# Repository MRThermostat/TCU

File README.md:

# TCU
hardware/software for thermostat control unit

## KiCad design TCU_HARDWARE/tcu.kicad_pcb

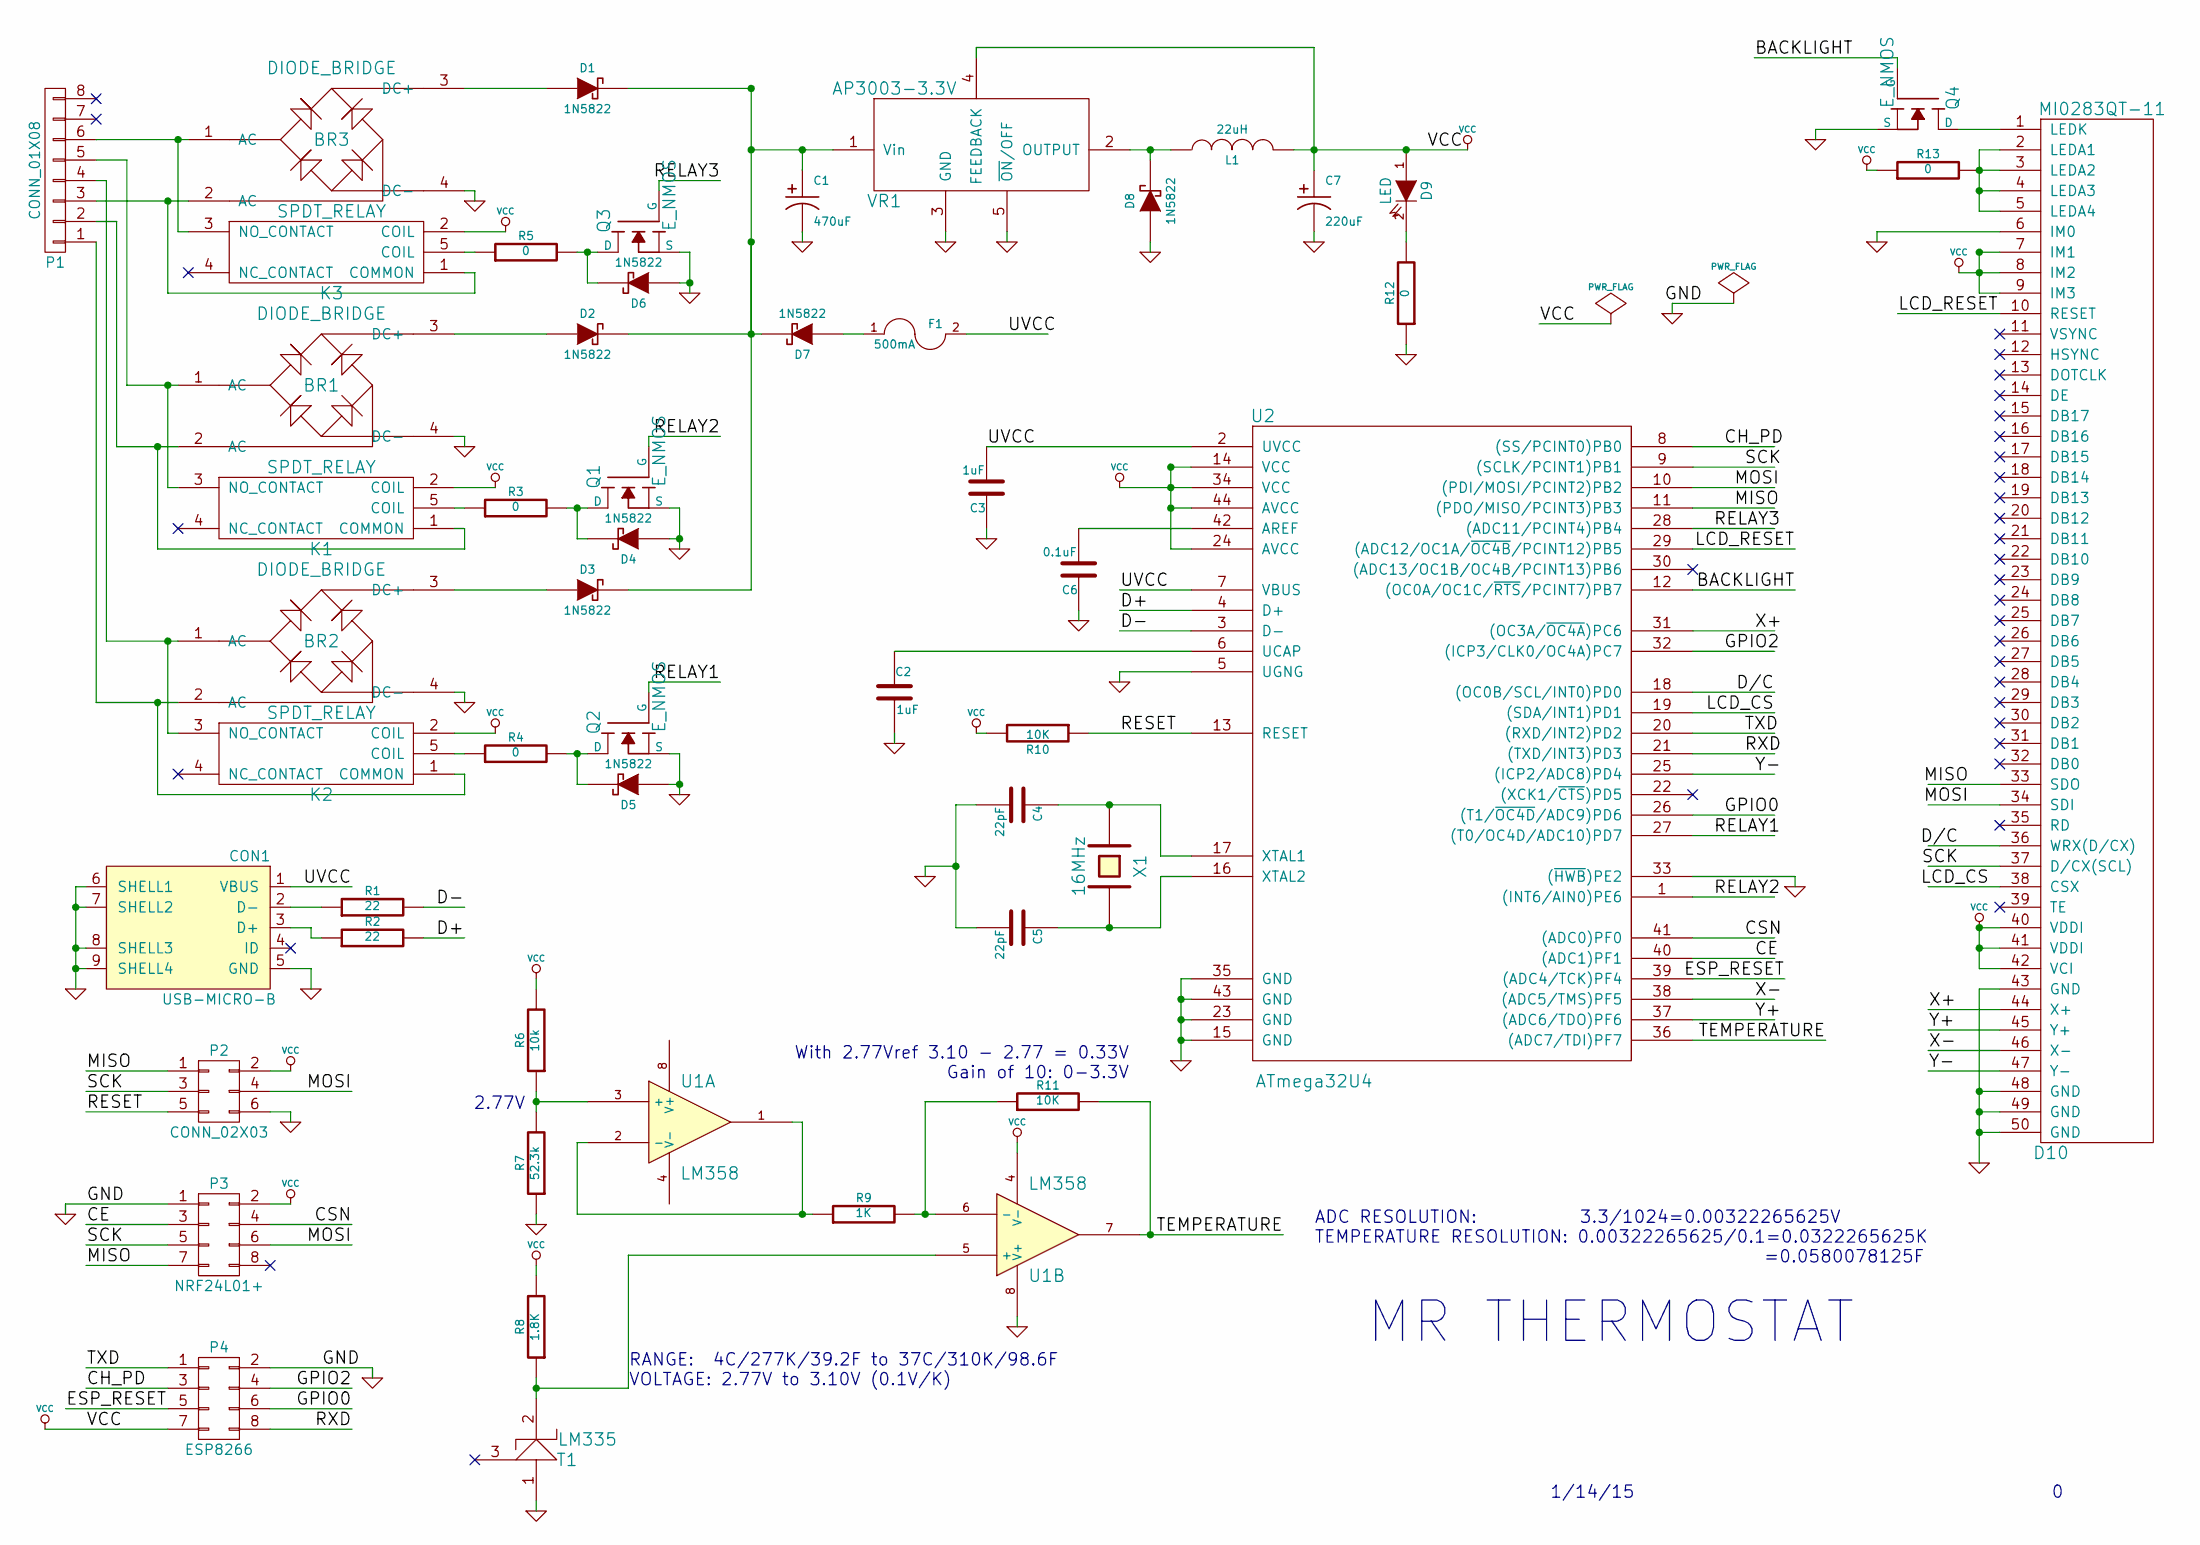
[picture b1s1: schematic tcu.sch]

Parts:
BR1, BR2, BR3: DIODE_BRIDGE; GBU4
C1: 470uF; CAP_POL_10
C2, C3: 1uF; C_0603_HandSoldering
C4, C5: 22pF; C_0603_HandSoldering
C6: 0.1uF; C_0603_HandSoldering
C7: 220uF; CAP_POL_6.3
CON1: USB-MICRO-B; USB_Micro-B
D1, D2, D3, D4, D5, D6, D7, D8: 1N5822; DO-214-AA_SMB
D9: LED; LED-0603
D10: MI0283QT-11; FPC CONNECTOR
F1: 500mA; SMD-0603
K1, K2, K3: SPDT_RELAY; G5LE
L1: 22uH; SMD_Inductor
P1: CONN_01X08; 796638-8
P2: CONN_02X03; Pin_Header_Straight_2x03
P3: NRF24L01+
P4: ESP8266
Q1, Q2, Q3, Q4: E_NMOS; SOT-23-GDS
R1, R2: 22; R_0603_HandSoldering
R3, R4, R5, R12, R13: 0; R_0603_HandSoldering
R6: 10k; R_0603_HandSoldering
R7: 52.3k; R_0603_HandSoldering
R8: 1.8K; R_0603_HandSoldering
R9: 1K; R_0603_HandSoldering
R10, R11: 10K; R_0603_HandSoldering
T1: LM335; TO-92-Free-molded-wide
U1: LM358; SOIC-8-W
U2: ATmega32U4; TQFP-44_10x10mm_Pitch0.8mm
VR1: AP3003-3.3V; TO-263-5_HandSoldering
X1: 16MHz; Crystal_HC49-U_Vertical

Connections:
/BACKLIGHT: Q4.G, U2.12 ((OC0A/OC1C/~RTS~/PCINT7)PB7)
/CE: P3.3, U2.40 ((ADC1)PF1)
/CH_PD: P4.3, U2.8 ((SS/PCINT0)PB0)
/CSN: P3.4, U2.41 ((ADC0)PF0)
/D+: R2.2, U2.4 (D+)
/D-: R1.2, U2.3 (D-)
/D/C: D10.36 (WRX(D/CX)), U2.18 ((OC0B/SCL/INT0)PD0)
/ESP_RESET: P4.5, U2.39 ((ADC4/TCK)PF4)
/GPIO0: P4.6, U2.26 ((T1/~OC4D~/ADC9)PD6)
/GPIO2: P4.4, U2.32 ((ICP3/CLK0/OC4A)PC7)
/LCD_CS: D10.38 (CSX), U2.19 ((SDA/INT1)PD1)
/LCD_RESET: D10.10 (RESET), U2.29 ((ADC12/OC1A/~OC4B~/PCINT12)PB5)
/MISO: D10.33 (SDO), P2.1, P3.7, U2.11 ((PDO/MISO/PCINT3)PB3)
/MOSI: D10.34 (SDI), P2.4, P3.6, U2.10 ((PDI/MOSI/PCINT2)PB2)
/RELAY1: Q2.G, U2.27 ((T0/OC4D/ADC10)PD7)
/RELAY2: Q1.G, U2.1 ((INT6/AIN0)PE6)
/RELAY3: Q3.G, U2.28 ((ADC11/PCINT4)PB4)
/RESET: P2.5, R10.1, U2.13 (RESET)
/RXD: P4.8, U2.21 ((TXD/INT3)PD3)
/SCK: D10.37 (D/CX(SCL)), P2.3, P3.5, U2.9 ((SCLK/PCINT1)PB1)
/TEMPERATURE: R11.2, U1.7, U2.36 ((ADC7/TDI)PF7)
/TXD: P4.1, U2.20 ((RXD/INT2)PD2)
/UVCC: C3.2, CON1.1 (VBUS), F1.2, U2.2 (UVCC), U2.7 (VBUS)
/X+: D10.44 (X+), U2.31 ((OC3A/~OC4A~)PC6)
/X-: D10.46 (X-), U2.38 ((ADC5/TMS)PF5)
/Y+: D10.45 (Y+), U2.37 ((ADC6/TDO)PF6)
/Y-: D10.47 (Y-), U2.25 ((ICP2/ADC8)PD4)
GND: BR1.4 (DC-), BR2.4 (DC-), BR3.4 (DC-), C1.2, C2.2, C3.1, C4.2, C5.2, C6.1, C7.2, CON1.5 (GND), CON1.6 (SHELL1), CON1.7 (SHELL2), CON1.8 (SHELL3), CON1.9 (SHELL4), D4.1 (A), D5.1 (A), D6.1 (A), D8.1 (A), D10.6 (IM0), D10.43 (GND), D10.48 (GND), D10.49 (GND), D10.50 (GND), P2.6, P3.1, P4.2, Q1.S, Q2.S, Q3.S, Q4.S, R7.1, R12.1, T1.1, U1.8 (V+), U2.5 (UGNG), U2.15 (GND), U2.23 (GND), U2.33 ((~HWB~)PE2), U2.35 (GND), U2.43 (GND), VR1.3 (GND), VR1.5 (~ON~/OFF)
unnamed: BR1.1 (AC), K1.3 (NO_CONTACT), P1.5
unnamed: BR1.2 (AC), K1.1 (COMMON), P1.2
unnamed: BR1.3 (DC+), D2.1 (A)
unnamed: BR2.1 (AC), K2.3 (NO_CONTACT), P1.4
unnamed: BR2.2 (AC), K2.1 (COMMON), P1.1
unnamed: BR2.3 (DC+), D3.1 (A)
unnamed: BR3.1 (AC), K3.3 (NO_CONTACT), P1.6
unnamed: BR3.2 (AC), K3.1 (COMMON), P1.3
unnamed: BR3.3 (DC+), D1.1 (A)
unnamed: C1.1, D1.2 (K), D2.2 (K), D3.2 (K), D7.2 (K), VR1.1 (Vin)
unnamed: C2.1, U2.6 (UCAP)
unnamed: C4.1, U2.17 (XTAL1), X1.1
unnamed: C5.1, U2.16 (XTAL2), X1.2
unnamed: C6.2, U2.42 (AREF)
unnamed: CON1.2 (D-), R1.1
unnamed: CON1.3 (D+), R2.1
unnamed: D4.2 (K), Q1.D, R3.2
unnamed: D5.2 (K), Q2.D, R4.2
unnamed: D6.2 (K), Q3.D, R5.2
unnamed: D7.1 (A), F1.1
unnamed: D8.2 (K), L1.1, VR1.2 (OUTPUT)
unnamed: D9.2 (K), R12.2
unnamed: D10.1 (LEDK), Q4.D
unnamed: D10.2 (LEDA1), D10.3 (LEDA2), D10.4 (LEDA3), D10.5 (LEDA4), R13.2
unnamed: K1.5 (COIL), R3.1
unnamed: K2.5 (COIL), R4.1
unnamed: K3.5 (COIL), R5.1
unnamed: R6.1, R7.2, U1.3 (+)
unnamed: R8.1, T1.2, U1.5 (+)
unnamed: R9.1, U1.1, U1.2 (-)
unnamed: R9.2, R11.1, U1.6 (-)
VCC: C7.1, D9.1 (A), D10.7 (IM1), D10.8 (IM2), D10.9 (IM3), D10.40 (VDDI), D10.41 (VDDI), D10.42 (VCI), K1.2 (COIL), K2.2 (COIL), K3.2 (COIL), L1.2, P2.2, P3.2, P4.7, R6.2, R8.2, R10.2, R13.1, U1.4 (V-), U2.14 (VCC), U2.24 (AVCC), U2.34 (VCC), U2.44 (AVCC), VR1.4 (FEEDBACK)

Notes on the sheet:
MR THERMOSTAT
1/14/15
RANGE: 4C/277K/39.2F to 37C/310K/98.6F VOLTAGE: 2.77V to 3.10V (0.1V/K)
ADC RESOLUTION: 3.3/1024=0.00322265625V TEMPERATURE RESOLUTION: 0.00322265625/0.1=0.0322265625K =0.0580078125F
2.77V
With 2.77Vref 3.10 - 2.77 = 0.33V Gain of 10: 0-3.3V

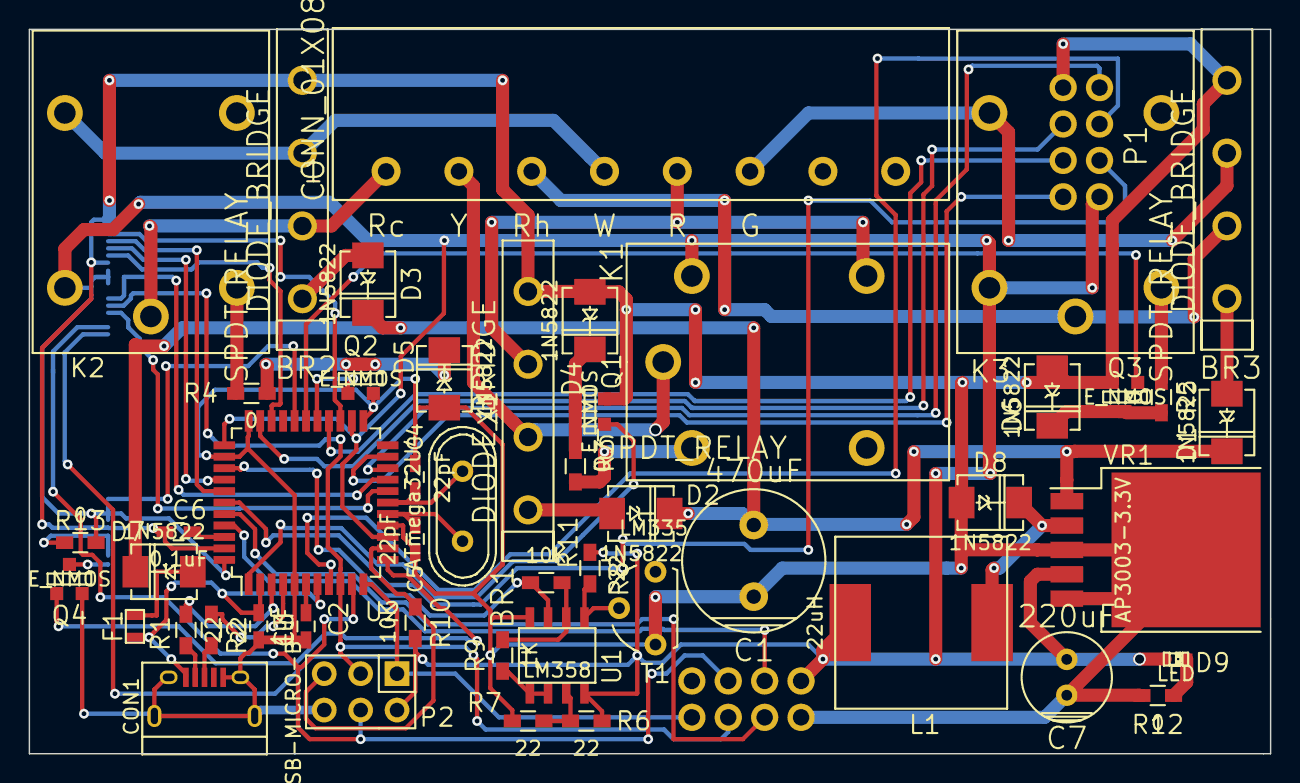
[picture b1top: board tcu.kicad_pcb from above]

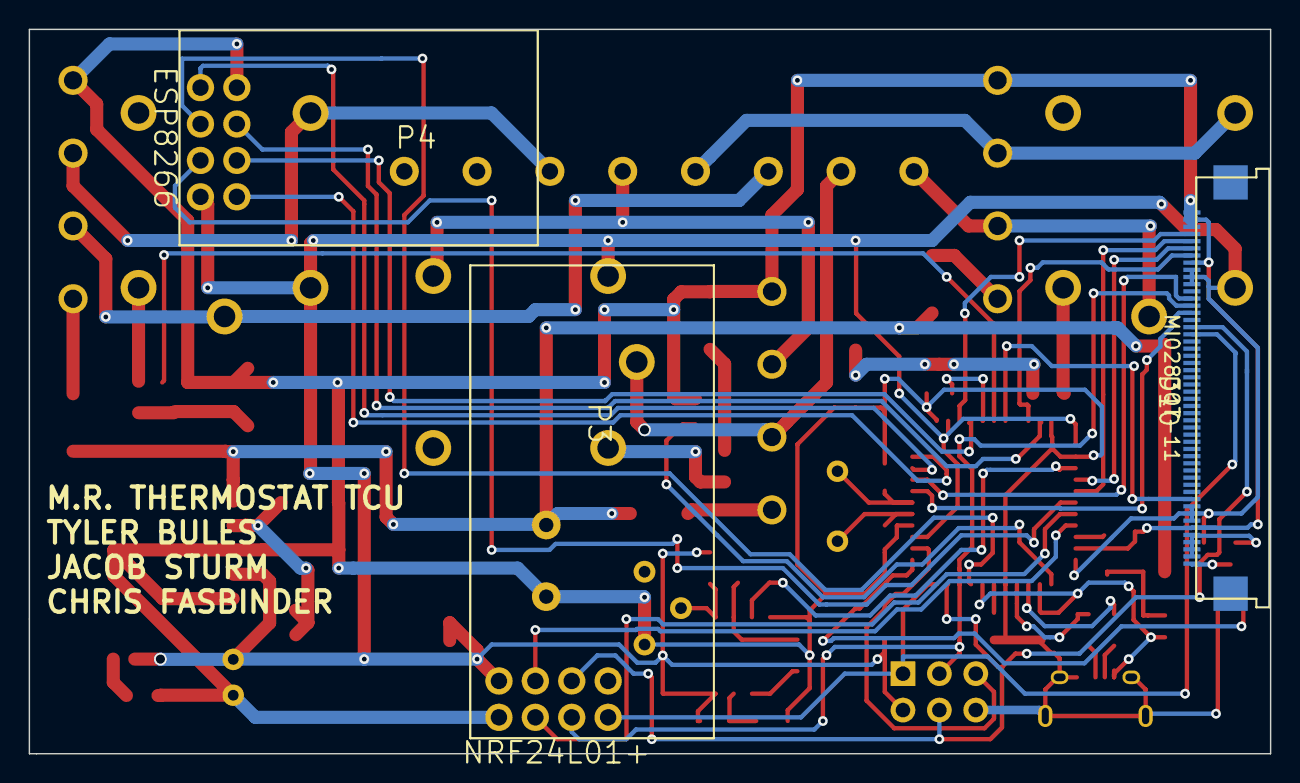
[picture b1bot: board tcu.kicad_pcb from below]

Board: 2 copper layers, 86.6 x 50.5 mm, 52 parts (3 on the bottom side), 60 nets.

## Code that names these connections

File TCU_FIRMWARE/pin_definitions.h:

//touchscreen pins
#define YP A1
#define XM A2
#define YM 4
#define XP 5

//lcd control pins
#define TFT_CS 2
#define TFT_DC 3
#define TFT_RESET 9
#define TFT_BACKLIGHT 11

//nrf24l01 control pins
#define NRF_CE A4
#define NRF_CSN A5

//esp8266 control pins
#define ESP_GPIO0 12
#define ESP_GPIO2 13
#define ESP_RESET A3
#define ESP_CH_PD 14

//temperature reading
#define TEMP_PIN A0

//relay control pins
#define RELAY1 6
#define RELAY2 7
#define RELAY3 8

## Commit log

2015-01-27 schematic finished, footprints in progress
2015-01-27 Revert "Initial commit"
    This reverts commit 99d7021763783f5f3b765942d3dde8338172b6d3.
2015-01-27 cleared out the clusterfuck
2015-01-27 replaced clusterfuck
    schematic finished, footprints in progress
2015-01-27 assigned footprint for p2, vr1, p4
2015-01-27 assigned footprints
    d1-d8, U1,t1,
2015-01-27 cleaned up datasheets, added datasheet for lcd connector clip
2015-01-28 created and assigned display connector footprint
2015-01-28 added readme so github will be happy
    This repositor contains hardware and software for the thermostat control unit of the Mr. Thermostat project.
2015-01-28 fuse footprint selected
2015-01-28 created and assigned inductor footprint
2015-01-28 finished footprints... hopefully
2015-01-28 started routing
    external connections mostly done
2015-01-29 further work on layout
2015-01-29 squeezing in
2015-01-29 moved left and right relay up
    everything should fit vertically behind screen
2015-01-29 touchscreen routed
2015-01-29 almost done routing lcd
2015-02-01 began routing wifi modules
2015-02-01 esp8266 at bottom
2015-02-01 ALL ROUTING COMPLETE
2015-02-01 normalized fonts and aligned references
    also rerouted backlight trace
2015-02-01 generated, renamed, and packaged gerbers
2015-02-01 fixed fastbinder to fasbinder
    new gerbers generated and packaged. sending for quote.
2015-02-01 ordered first batch
2015-02-03 modified folder structure. preparing for software
2015-02-04 added pin definitions
2015-02-04 opened serial channel on setup
2015-02-04 added touchscreen library
2015-02-10 Testing
    Backing up to protect from crashing
2015-02-10 same
2015-02-12 Legit Branch
    Has mainscreen and profile settings GUI with fixed orientation.
2015-02-12 More Screens Added
    Added profile edit and rules edit screen
2015-02-16 activeList GUI created
    Added some missing ;
    Added GUI for setting a sensor to active/not active
2015-02-17 Sensor Info
    added sensor info gui and edited active sensor list gui
2015-02-17 Sensor Info
    some changes did not go through
2015-02-19 Creating Keyboard
    Added keyboard(not fully functional yet), may move to its own header
2015-02-19 added functions for acquiring temperature
    still work to be done. may be hardware related
2015-02-20 added wifi file and functions
2015-02-20 Touch Functionality to Keyboard
    Added function to handle touch keyboard
    needs a little work
2015-02-23 Keyboard and HVAC
    finished the touch recognition for keyboard and started on the HVAC
    settings
2015-02-24 created new board device
    pin definitions moved to board definitions pins_arduino.h
    implemented external library to control ESP8266
    LCD has been brought to life. preparing to pull in chris's branch.
2015-02-26 Drawing method redone for performance
    1. Redone:
    mainScreen
    changeTemp
    profileSettings
    2. New function unitPos added
    3. Started touchscreen implementation
2015-02-26 More Screens
    1. Redone:
    hvacSettings
    settings
    2. New Functions added
    cal(character array length)
    centerText
2015-02-26 Small Bug fix
    Misplaced do{, caused unnecessary screen reloads
2015-02-26 More Screens
    1. Redone:
    sensorSettings
    sensorEdit
    2. More Touchscreen implementation
    few screens are left
2015-03-04 Optimization
    Created printText, makeTitle, doubleLine functions to reduce memory
    usage. Went from 73% to 68%. Most screens functional
    Sketch uses 19,520 bytes (68%) of program storage space. Maximum is
    28,672 bytes.
    Global variables use 819 bytes (31%) of dynamic memory, leaving 1,741
    bytes for local variables. Maximum is 2,560 bytes.
2015-03-04 Added function
    Unused, but added displayList. May be useful in future.
2015-03-09 Storage
    Stores HVAC settings in EEPROM. Also able to write to the EEPROM
2015-03-10 prep for pull request
2015-03-10 partial merge
2015-03-10 still merging....
    working on pin definitions
2015-03-10 not using defs in pins_arduino
2015-03-10 merged, work from here
2015-03-10 wifi module setup
2015-03-13 Fixed unit conversion
    Corrected K to F conversion
    had -32 needed +32
2015-03-13 Changed lines 23, 27, 31, 35, 39
    Was assigning to x instead of comparing.
2015-03-13 Previous Fixes
    Bugs I noticed after the pull request
2015-03-14 Made Functional
    Getting my branch to work
2015-03-14 works with lcd now
    finished and tested EEPROM writing and reading functions.
    Will not save and restore wifi credentials in EEPROM
    Credentials displayed on wifi settings screen
2015-03-15 gui updates
    all lines, both vertical and horizontal should be double lines now
    wifisetup screen tested. gives user instructions and dynamic IP address
    is provided.
    wifi side of things is not implemented yet.
    moved around some text in wifi settings
2015-03-18 Near fully functional Sensor Page
    Sensor page now pulls from eeprom
    added functions to add and remove sensor from list
2015-03-19 Main Screen near fully functional
    HVAC settings connected to eeprom
    Current temp connected to eeprom
    Desired temp connected to eeprom
    Cycle Sensor List fully functional
2015-03-19 Code Cleanup
    Now up to date with master branch.
    Added draw.h
    contains doubleHLine, doubleVLine, printText, cal, centerText,
    makeTitle, and unitPos
    Added sensors.h
    containts addSensor, removeSensor, sensorBytes, and cycleSensorList
2015-03-24 wifi setup goods
2015-03-24 trying to get wifi setup to work.
    reply formatted correctly now
2015-03-27 Profiles
    Working with profiles to get them attached to eeprom and create
    functions to handle them
2015-03-28 still not working
2015-03-29 condense wifi code
2015-03-31 Profiles
    Fully functional profile page.
    pulls from eeprom
    functions to add/delete/edit profiles and rules
